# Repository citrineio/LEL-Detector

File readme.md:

# Project Description

This project takes inspiration from my current job as a control and instrumentation engineer in the oil and gas industry. We have to deal with the risk of combustible or toxic gases leaks and one of the mandatory protection mechanisms is having a gas detection system. I designed a detector for combustible gases especially H2 which utilizes a common communication protocol to send data to the main controller in the system. 

This project incorporates the following: 
- SGP30 air quality sensor with H2 detection capability
- STM32F103 microcontroller
- LTC2631ITS8 I2C DAC with voltage output
- AD5749 4-20mA transmitter IC to send data to a connector and then to the control system.
- AOM12864A0 1.54" OLED display for reading the sensor's value.
- Two Omron relays for controlling and signaling an alarm light and a horn during a gas leak.

## Block Diagram

## Board Images

## Repository Guide:

### 3D:

3D model of the PCB, 3D models of the components are also available in the dedicated folder.

### PCB Layout: 

The latest Kicad PCB layout file is here. You can find component land patterns (aka footprints) in the dedicated folder.

### Schematics:

The latest Kicad schematics capture files are here. PDF version will be updated weekly during the schematics capture phase. You can also find the schematics symbols in the dedicated folder.

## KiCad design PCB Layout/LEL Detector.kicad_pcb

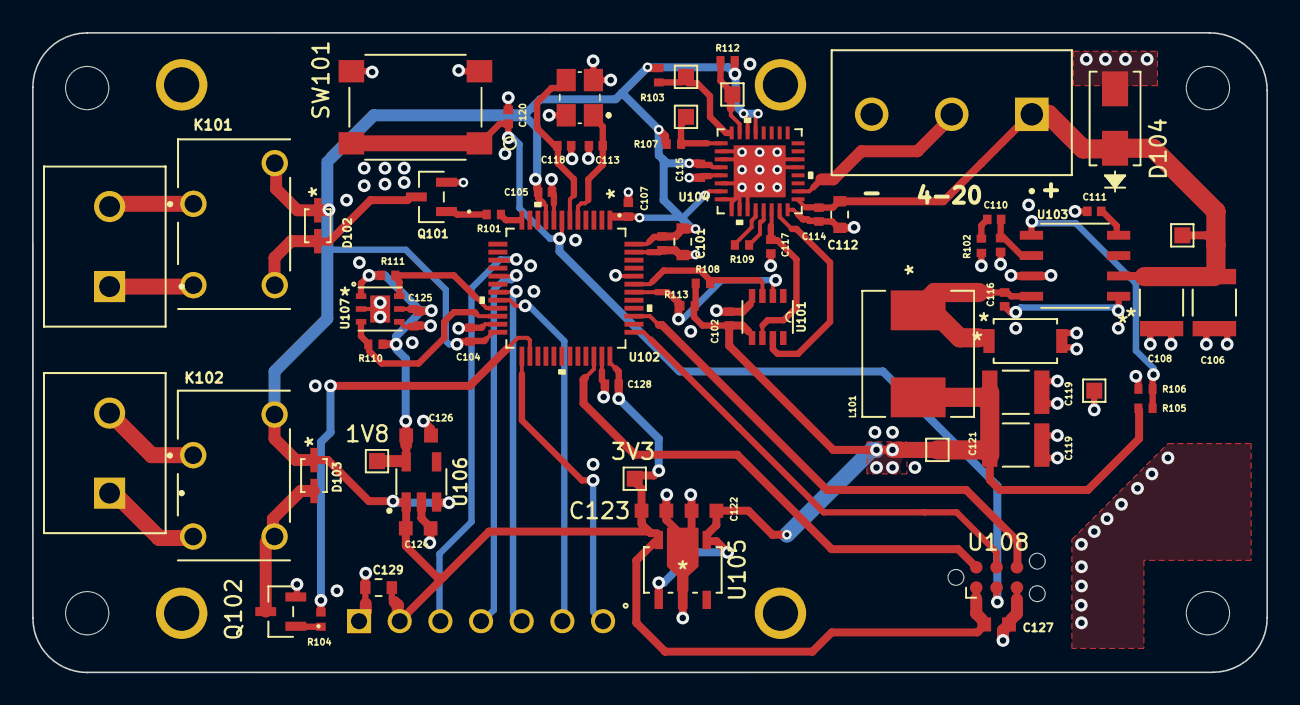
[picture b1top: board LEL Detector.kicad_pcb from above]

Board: 4 copper layers, 77.1 x 39.9 mm, 77 parts (1 on the bottom side), 44 nets.

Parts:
1V8, 3V3, 5V101, 24V101: TestPoint; TestPoint_Pad_1.0x1.0mm
C101, C112, C129: 10u; SAMSUNG_10u_0603
C102, C103, C104, C105, C107, C114, C115, C116, C120, C125, C128: 100n; CAPC1005X55N_1n2
C106, C108: 10u; CAPC3225X270N_10U
C109: 1p; CAPC1005X55N_1n2
C110: 1n2; CAPC1005X55N_1n2
C111: 8n2; CAPC1005X55N_1n2
C113, C118: 10p; CAPC1005X55N_1n2
C117: 330n; CAPC1005X55N_330n
C119, C121: 47u; CAPC3225X270N_10U
C122, C123, C124, C126, C127: 4u7; MURATA_4u7_0603
D101: 30v; RB080LAM-30TR
D102, D103: SOD-323_SDS; 1N4148WSTR
D104: D_Zener; SMAJ40A-13-F_TVS
DS101: AOM12864A0-1.54WW-ANO; AOM12864A0-1.54WW-ANO_DISPLAY
GND101: TestPoint; TestPoint_Pad_1.0x1.0mm
H101, H102, H103, H104: M2.5; MountingHole_2.7mm_M2.5
IFAULT101: TestPoint; TestPoint_Pad_1.0x1.0mm
J102: TB003-500-P03BE; CUI_TB003-500-P03BE
J103, J104: TB002-500-02BE; CUI_TB002-500-02BE
K101, K102: G6L-1P-DC3; RELAY_G6L-1P-DC3
L101: 8u2; IHLP2525CZER8R2M01
Q101, Q102: DMN65D8L-7; DMN65D8L-7_MOSFET
R101, R104, R106: 1K96; RESC1005X40N
R102: 34K; RESC1005X40N
R103, R107, R112: 100k; RESC1005X40N
R105, R110, R111: 10K2; RESC1005X40N
R108, R113: 2K2; RESC1005X40N_2K2
R109: 15K; RESC1005X40N
SW101: B3FS-1002P; B3FS-1002P_BUTTON
TEMP101: TestPoint; TestPoint_Pad_1.0x1.0mm
U101: SOT-8_TS_LIT; LTC2631ITS8-HZ10-TRMPBF
U102: LQFP48-7x7mm; STM32F103C8T6
U103: D8; TPS54331DR
U104: CP_32_2_ADI; AD5749ACPZ
U105: SOT89-5_DIO; AP7361C-33Y5-13
U106: TLV74118PDBVR; SOT95P280X145-5N_1V8
U107: SGP30-2.5K_SEN; SGP30-2.5K
U108: TC2030-IDC-NL; Tag-Connect_TC2030-IDC-NL_2x03_P1.27mm_Vertical
VFAULT101: TestPoint; TestPoint_Pad_1.0x1.0mm
Y101: Crystal; ABM8G16000MHZB4YT

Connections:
+1V8: 1V8.1, C125.2, C126.1, R110.1, R111.1, U106.5 (OUT), U107.1 (VDD), U107.5 (VDDH)
+3.3V: 3V3.1, C101.1, C103.2, C104.2, C105.2, C107.2, C115.2, C123.1, C124.1, C127.1, C128.2, C129.1, D102.1 (K), D103.1 (K), DS101.2 (VDD), K101.8, K102.8, R103.1, R107.1, R112.1, U102.1 (VBAT), U102.9 (VDDA), U102.24 (VDD_1), U102.36 (VDD_2), U102.48 (VDD_3), U104.4 (DVCC), U104.7 (SCLK/OUTEN), U104.29 (HWSELECT), U104.30 (*RESET), U105.5 (OUT), U106.1 (IN), U106.3 (EN), U108.1 (VCC)
+5V: 5V101.1, C102.2, C119.1, C121.1, C122.1, L101.2, R105.1, R108.1, R113.1, U101.5 (VCC), U105.1 (EN), U105.4 (VIN)
+24V: 24V101.1, C106.1, C108.1, C112.1, C114.2, D104.1 (K), J102.1, U103.2 (VIN), U104.17 (AVDD)
/4_20MA: J102.2, U104.18 (IOUT)
/ALARM_HORN: R104.1, U102.26 (PB13)
/ALARM_LGHT: R101.1, U102.12 (PA2)
/BOOT: C116.1, U103.1 (BOOT)
/COMP: C109.1, C110.1, U103.6 (COMP)
/DAC_VOUT: U101.7 (VOUT), U104.15 (VIN)
/DISP_DC: DS101.6 (DC), U102.20 (PB2)
/DISP_RST: DS101.5 (RST), U102.19 (PB1)
/Fault: R107.2, U104.1 (SDO/VFAULT), VFAULT101.1
/HORN_D: D103.2 (A), K102.5, Q102.3 (D)
/HORN_G: Q102.1 (G), R104.2
/I2C1_SCL: R113.2, U101.2 (SCL), U102.42 (PB6)
/I2C1_SDA: R108.2, U101.3 (SDA), U102.43 (PB7)
/I2C2_SCL: R111.2, U102.21 (PB10), U107.6 (SCL)
/I2C2_SDA: R110.2, U102.22 (PB11), U107.3 (SDA)
/IFAULT: IFAULT101.1, R103.2, U104.32 (NC/IFAULT)
/LGHT_D: D102.2 (A), K101.5, Q101.3 (D)
/LGHT_G: Q101.1 (G), R101.2
/NRST: C120.2, SW101.1, SW101.2, U102.7 (NRST), U108.3 (nRESET)
/OSC_IN: C113.2, U102.5 (OSC_IN), Y101.1 (XIN)
/OSC_OUT: C118.2, U102.6 (OSC_OUT), Y101.3 (XOUT)
/PH: C116.2, D101.1 (K), L101.1, U103.8 (PH)
/RCOMP: C110.2, R102.1
/REXT1: R109.1, U104.12 (REXT2)
/REXT2: R109.2, U104.13 (REXT1)
/SPI1_CS: DS101.7 (CS), U102.25 (PB12)
/SPI1_MOSI: DS101.4 (SDA), U102.17 (PA7)
/SPI1_SCK: DS101.3 (SCL), U102.15 (PA5)
/SS: C111.1, U103.4 (SS)
/SWCLK: U102.37 (PA14), U108.4 (SWCLK_/_TCK)
/SWDIO: U102.34 (PA13), U108.2 (SWDIO/TMS)
/SWO: U102.39 (PB3), U108.6 (SWO_/_TDO)
/TEMP: R112.2, TEMP101.1, U104.31 (FAULT/TEMP)
/VREF: C117.2, U101.6 (REF), U104.14 (VREF)
/VSENSE: R105.2, R106.1, U103.5 (VSENSE)
GND: C101.2, C102.1, C103.1, C104.1, C105.1, C106.2, C107.1, C108.2, C109.2, C111.2, C112.2, C113.1, C114.1, C115.1, C117.1, C118.1, C119.2, C120.1, C121.2, C122.2, C123.2, C124.2, C125.1, C126.2, C127.2, C128.1, C129.2, D101.2 (A), D104.2 (A), DS101.1 (GND), GND101.1, J102.3, Q101.2 (S), Q102.2 (S), R102.2, R106.2, SW101.3, SW101.4, U101.4 (GND), U102.8 (VSSA), U102.23 (VSS_1), U102.35 (VSS_2), U102.44 (BOOT0), U102.47 (VSS_3), U103.7 (GND), U104.2 (CLRSEL), U104.3 (CLEAR), U104.5 (GND), U104.6 (*SYNC/RSET), U104.8 (SDIN/R0), U104.9 (AD2/R1), U104.10 (AD1/R2), U104.11 (AD0/R3), U104.16 (GND), U104.21 (GND), U104.22 (GND), U104.33 (EPAD), U105.2 (GND), U106.2 (GND), U107.2 (VSS), U107.4 (R), U107.7 (VSS), U108.5 (GND), Y101.2 (GND), Y101.4 (GND)
unnamed: J103.1, K101.4
unnamed: J103.2, K101.2
unnamed: J104.1, K102.4
unnamed: J104.2, K102.2

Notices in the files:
parts and their libraries:
Copyright 2021 Accelerated Designs. All rights reserved.
